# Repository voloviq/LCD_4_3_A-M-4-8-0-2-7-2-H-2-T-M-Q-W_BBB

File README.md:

# LCD_4_3_AM480272H2TMQW_BBB
LCD AM480272H2TMQW PCB board for Beaglebone Black

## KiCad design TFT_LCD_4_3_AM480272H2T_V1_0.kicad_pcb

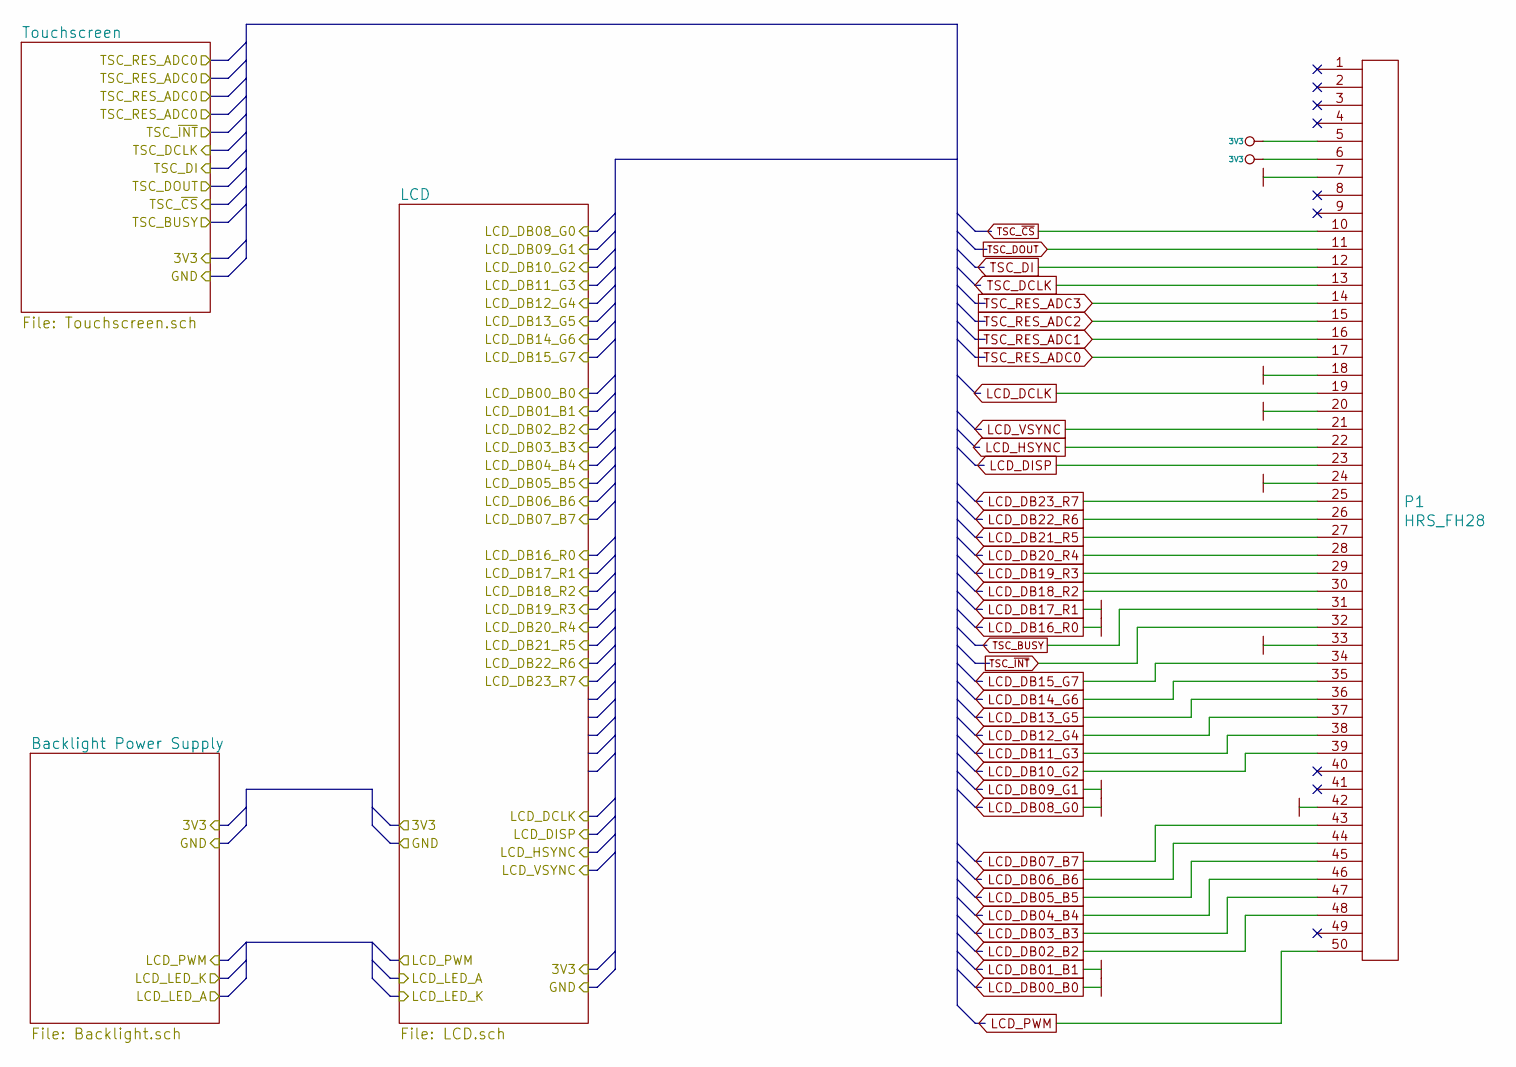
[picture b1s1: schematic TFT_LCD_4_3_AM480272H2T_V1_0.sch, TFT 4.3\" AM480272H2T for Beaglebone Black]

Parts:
P1: HRS_FH28; 50pin_HRS_FH28_0_5mm

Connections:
3V3: P1.5, P1.6; also elsewhere on the board
LCD_DB00_B0: P1.7, P1.18 (P8), P1.20 (P10), P1.24 (P4), P1.33 (P3), P1.42 (P2); also elsewhere on the board
LCD_DB02_B2: P1.48 (P8); also elsewhere on the board
LCD_DB03_B3: P1.47 (P7); also elsewhere on the board
LCD_DB04_B4: P1.46 (P6); also elsewhere on the board
LCD_DB05_B5: P1.45 (P5); also elsewhere on the board
LCD_DB06_B6: P1.44 (P4); also elsewhere on the board
LCD_DB07_B7: P1.43 (P3); also elsewhere on the board
LCD_DB10_G2: P1.39 (P9); also elsewhere on the board
LCD_DB11_G3: P1.38 (P8); also elsewhere on the board
LCD_DB12_G4: P1.37 (P7); also elsewhere on the board
LCD_DB13_G5: P1.36 (P6); also elsewhere on the board
LCD_DB14_G6: P1.35 (P5); also elsewhere on the board
LCD_DB15_G7: P1.34 (P4); also elsewhere on the board
LCD_DB18_R2: P1.30 (P10); also elsewhere on the board
LCD_DB19_R3: P1.29 (P9); also elsewhere on the board
LCD_DB20_R4: P1.28 (P8); also elsewhere on the board
LCD_DB21_R5: P1.27 (P7); also elsewhere on the board
LCD_DB22_R6: P1.26 (P6); also elsewhere on the board
LCD_DB23_R7: P1.25 (P5); also elsewhere on the board
LCD_DCLK: P1.19 (P9); also elsewhere on the board
LCD_DISP: P1.23 (P3); also elsewhere on the board
LCD_HSYNC: P1.22 (P2); also elsewhere on the board
LCD_PWM: P1.50 (P10); also elsewhere on the board
LCD_VSYNC: P1.21 (P1); also elsewhere on the board
TSC_DCLK: P1.13 (P3); also elsewhere on the board
TSC_DI: P1.12 (P2); also elsewhere on the board
TSC_DOUT: P1.11 (P1); also elsewhere on the board
TSC_RES_ADC0: P1.17 (P7); also elsewhere on the board
TSC_RES_ADC1: P1.16 (P6); also elsewhere on the board
TSC_RES_ADC2: P1.15 (P5); also elsewhere on the board
TSC_RES_ADC3: P1.14 (P4); also elsewhere on the board
TSC_~CS: P1.10; also elsewhere on the board
TSC_~INT: P1.32 (P2); also elsewhere on the board

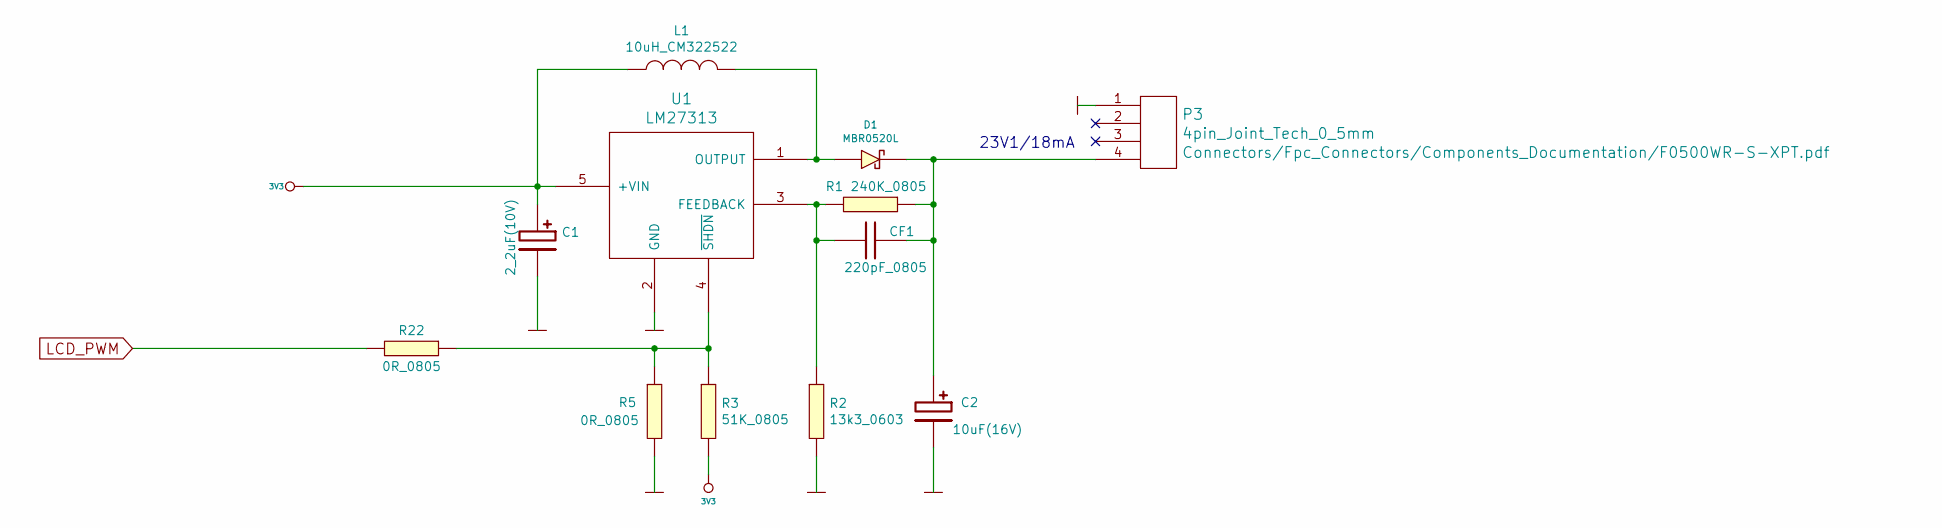
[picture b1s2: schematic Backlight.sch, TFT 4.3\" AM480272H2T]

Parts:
C1: 2_2uF(10V); 2_2uF_10V_A_Tantal
C2: 10uF(16V); 10uF_16V_B_Tantal
CF1: 220pF_0805
D1: MBR0520L; MBR0520L_SOD123
L1: 10uH_CM322522; DL1210_10uH
P3: 4pin_Joint_Tech_0_5mm
R1: 240K_0805; 240k_0805
R2: 13k3_0603
R3: 51K_0805; 51k_0805
R5, R22: 0R_0805
U1: LM27313; LM27313_SOT23

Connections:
3V3: C1.1, L1.1, R3.2, U1.5 (+VIN); also elsewhere on the board
LCD_DB00_B0: C1.2, C2.2, P3.1, R2.2, R5.2, U1.2 (GND); also elsewhere on the board
LCD_PWM: R22.2; also elsewhere on the board
unnamed: C2.1, CF1.1, D1.1 (K), P3.4, R1.1
unnamed: CF1.2, R1.2, R2.1, U1.3 (FEEDBACK)
unnamed: D1.2 (A), L1.2, U1.1 (OUTPUT)
unnamed: R3.1, R5.1, R22.1, U1.4 (~SHDN)

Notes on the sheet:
23V1/18mA

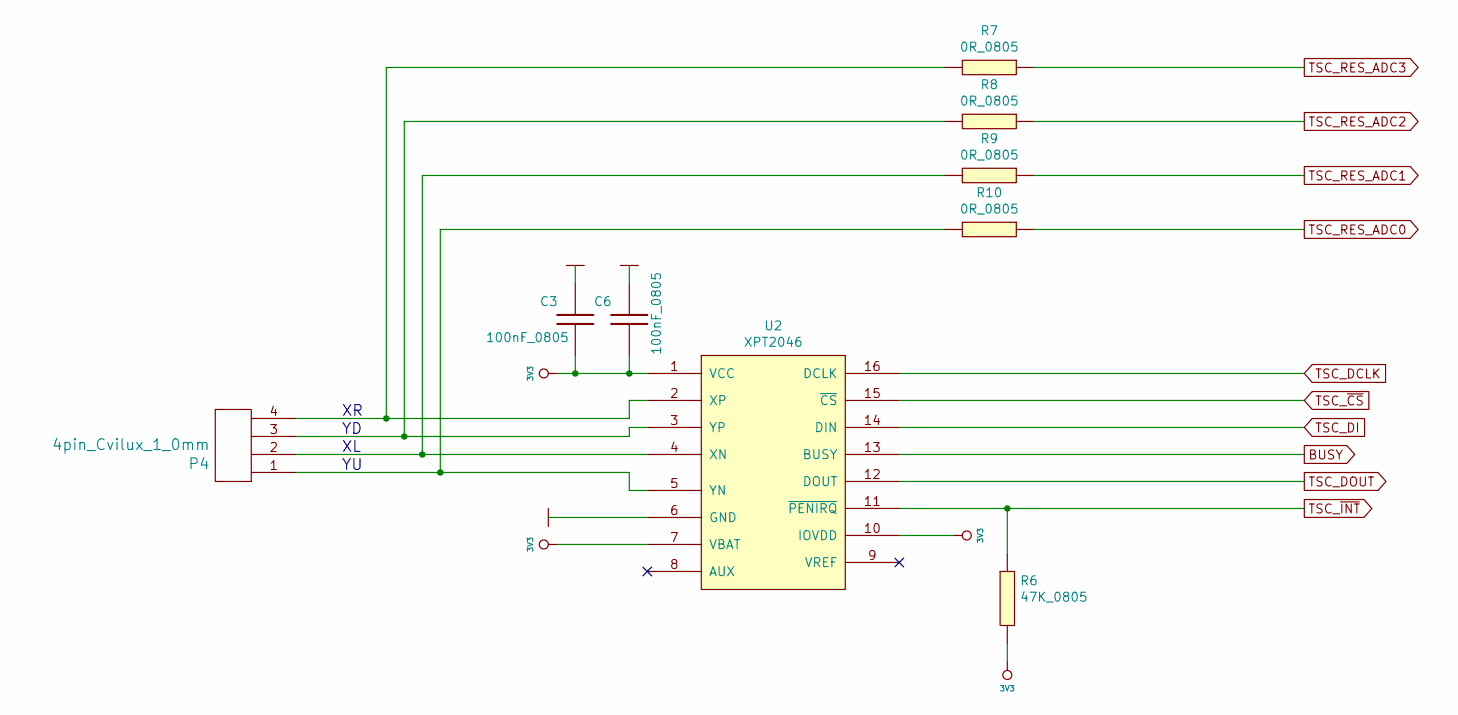
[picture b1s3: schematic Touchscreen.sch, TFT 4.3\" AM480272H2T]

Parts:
C3, C6: 100nF_0805
P4: 4pin_Cvilux_1_0mm
R6: 47K_0805; 47k_0805
R7, R8, R9, R10: 0R_0805
U2: XPT2046; XPT2046_TSSOP16

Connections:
3V3: C3.2, C6.2, R6.2, U2.1 (VCC), U2.7 (VBAT), U2.10 (IOVDD); also elsewhere on the board
LCD_DB00_B0: C3.1, C6.1, U2.6 (GND); also elsewhere on the board
unnamed: P4.1, R10.2, U2.5 (YN)
unnamed: P4.2, R9.2, U2.4 (XN)
unnamed: P4.3, R8.2, U2.3 (YP)
unnamed: P4.4, R7.2, U2.2 (XP)
TSC_DCLK: U2.16 (DCLK); also elsewhere on the board
TSC_DI: U2.14 (DIN); also elsewhere on the board
TSC_DOUT: U2.12 (DOUT); also elsewhere on the board
TSC_RES_ADC0: R10.1; also elsewhere on the board
TSC_RES_ADC1: R9.1; also elsewhere on the board
TSC_RES_ADC2: R8.1; also elsewhere on the board
TSC_RES_ADC3: R7.1; also elsewhere on the board
TSC_~CS: U2.15 (~CS); also elsewhere on the board
TSC_~INT: R6.1, U2.11 (~PENIRQ); also elsewhere on the board

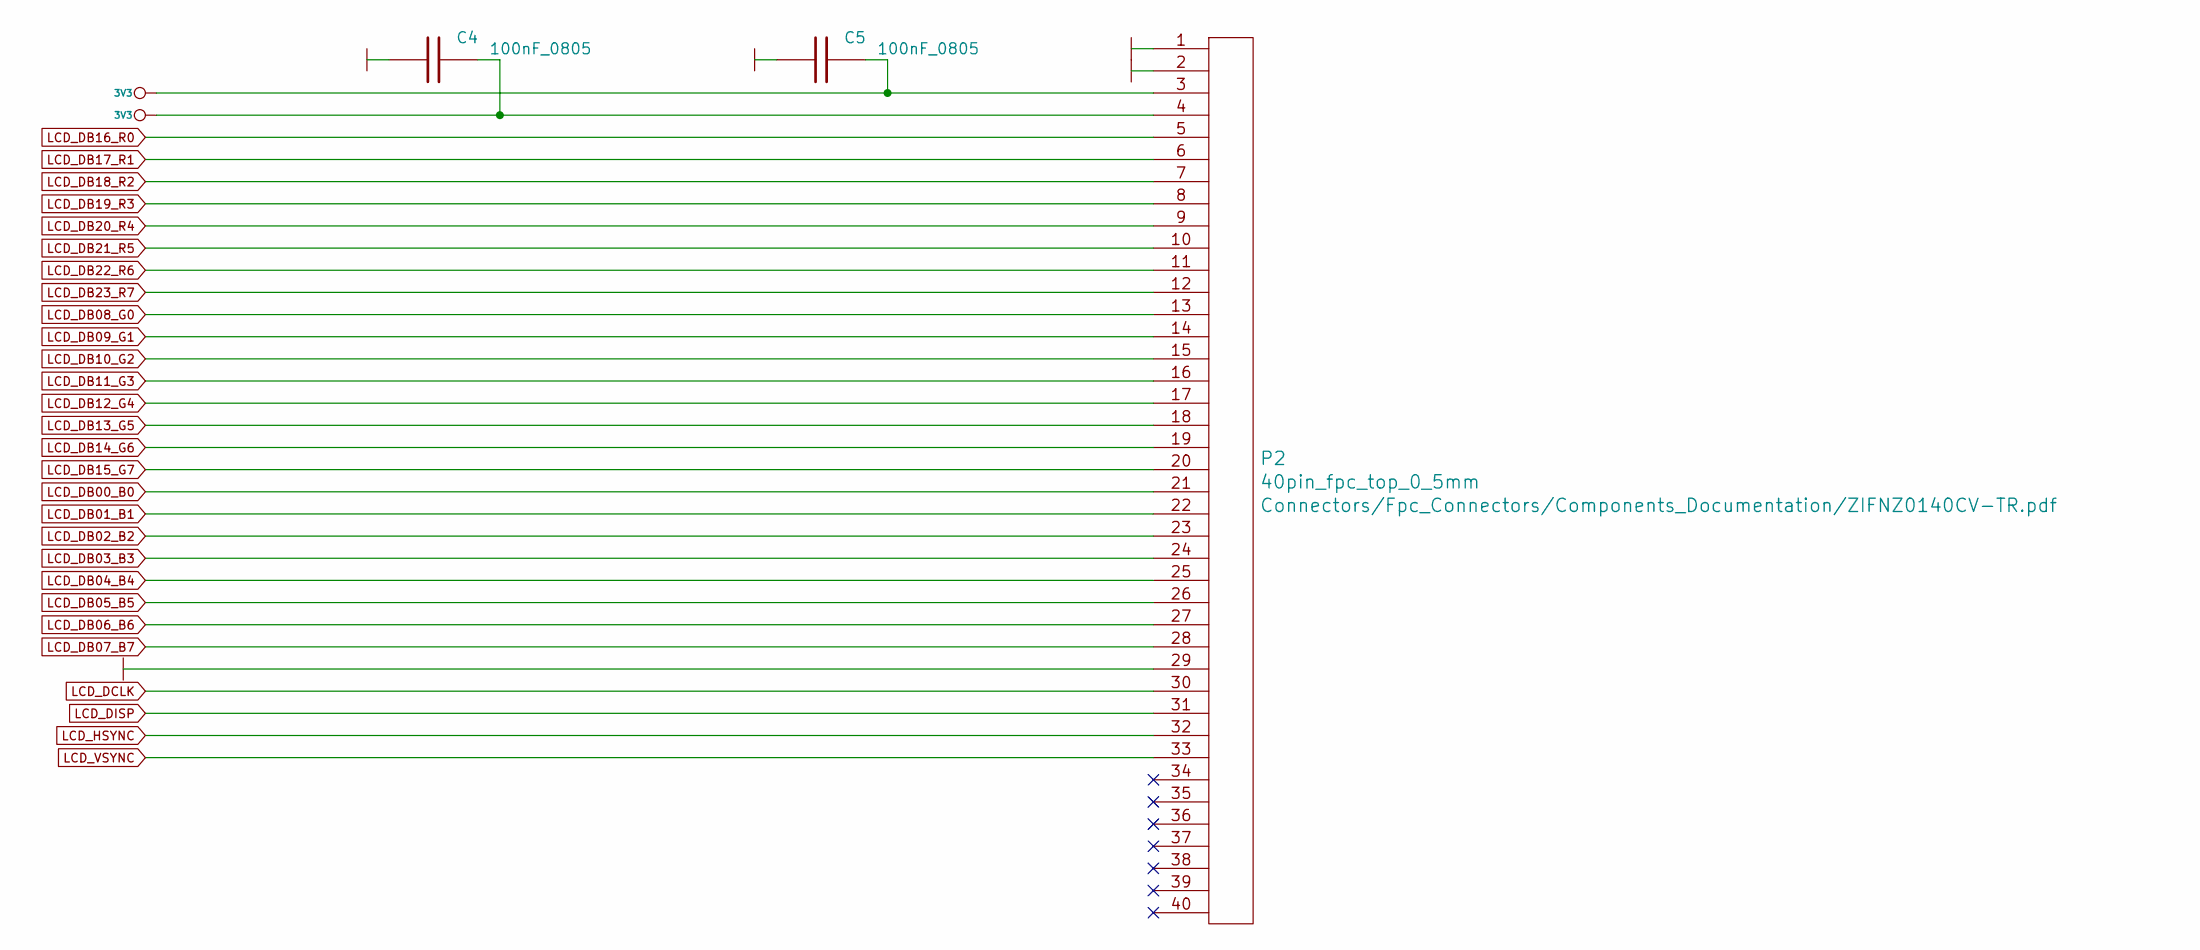
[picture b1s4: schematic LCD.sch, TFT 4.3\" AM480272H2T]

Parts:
C4, C5: 100nF_0805
P2: 40pin_fpc_top_0_5mm

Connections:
3V3: C4.1, C5.1, P2.3, P2.4; also elsewhere on the board
LCD_DB00_B0: C4.2, C5.2, P2.1, P2.2, P2.5, P2.6, P2.13 (P3), P2.14 (P4), P2.21 (P1), P2.22 (P2), P2.29 (P9); also elsewhere on the board
LCD_DB02_B2: P2.23 (P3); also elsewhere on the board
LCD_DB03_B3: P2.24 (P4); also elsewhere on the board
LCD_DB04_B4: P2.25 (P5); also elsewhere on the board
LCD_DB05_B5: P2.26 (P6); also elsewhere on the board
LCD_DB06_B6: P2.27 (P7); also elsewhere on the board
LCD_DB07_B7: P2.28 (P8); also elsewhere on the board
LCD_DB10_G2: P2.15 (P5); also elsewhere on the board
LCD_DB11_G3: P2.16 (P6); also elsewhere on the board
LCD_DB12_G4: P2.17 (P7); also elsewhere on the board
LCD_DB13_G5: P2.18 (P8); also elsewhere on the board
LCD_DB14_G6: P2.19 (P9); also elsewhere on the board
LCD_DB15_G7: P2.20 (P10); also elsewhere on the board
LCD_DB18_R2: P2.7; also elsewhere on the board
LCD_DB19_R3: P2.8; also elsewhere on the board
LCD_DB20_R4: P2.9; also elsewhere on the board
LCD_DB21_R5: P2.10; also elsewhere on the board
LCD_DB22_R6: P2.11 (P1); also elsewhere on the board
LCD_DB23_R7: P2.12 (P2); also elsewhere on the board
LCD_DCLK: P2.30 (P10); also elsewhere on the board
LCD_DISP: P2.31 (P1); also elsewhere on the board
LCD_HSYNC: P2.32 (P2); also elsewhere on the board
LCD_VSYNC: P2.33 (P3); also elsewhere on the board

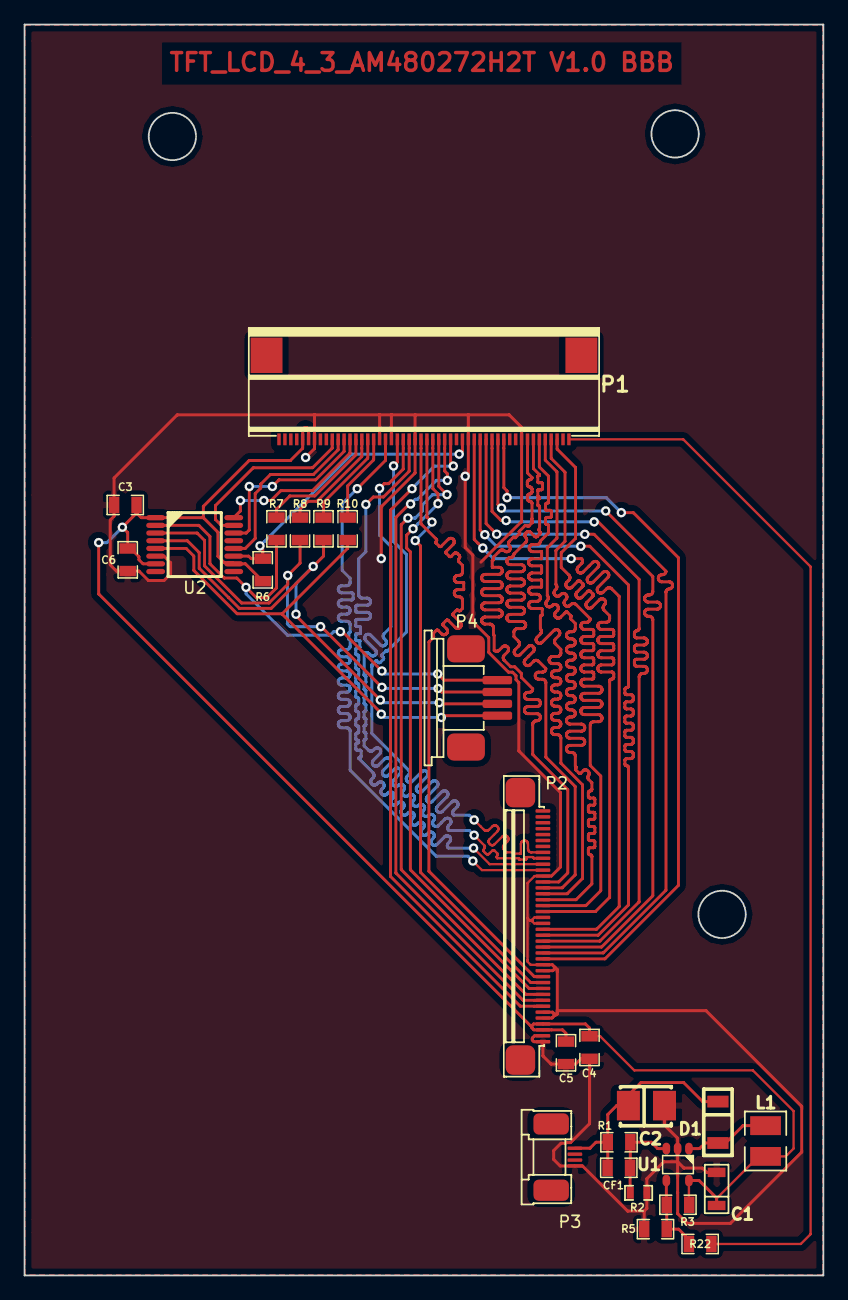
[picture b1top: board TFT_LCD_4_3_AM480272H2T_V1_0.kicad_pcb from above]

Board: 2 copper layers, 67.5 x 105.7 mm, 25 parts (0 on the bottom side), 42 nets.

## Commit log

2017-10-27 Initial
2017-10-28 Schematic finished, needes to be rechecked, pcb finished needes to be tweeked
2017-10-29 PCB tweaked, schematic still needes to be crosscheck, pcb fpc/fcc and bbb placement not checked yet
2017-10-29 Schematic crosscheck needed, FPC/FFC conntector needes to be place aligement
2017-11-23 Corrected FPC 40pin top 0.5mm connector, generated again gerber and ps files
